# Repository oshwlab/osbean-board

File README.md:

OSBean Boards
==============
OSBean的[开源硬件](http://www.oshwa.org/)项目。

WRTnodeShield
==============
OSBean针对WRTnode的扩展板。

电路原理图和PCB均采用[KiCad](www.kicad-pcb.org)软件完成。

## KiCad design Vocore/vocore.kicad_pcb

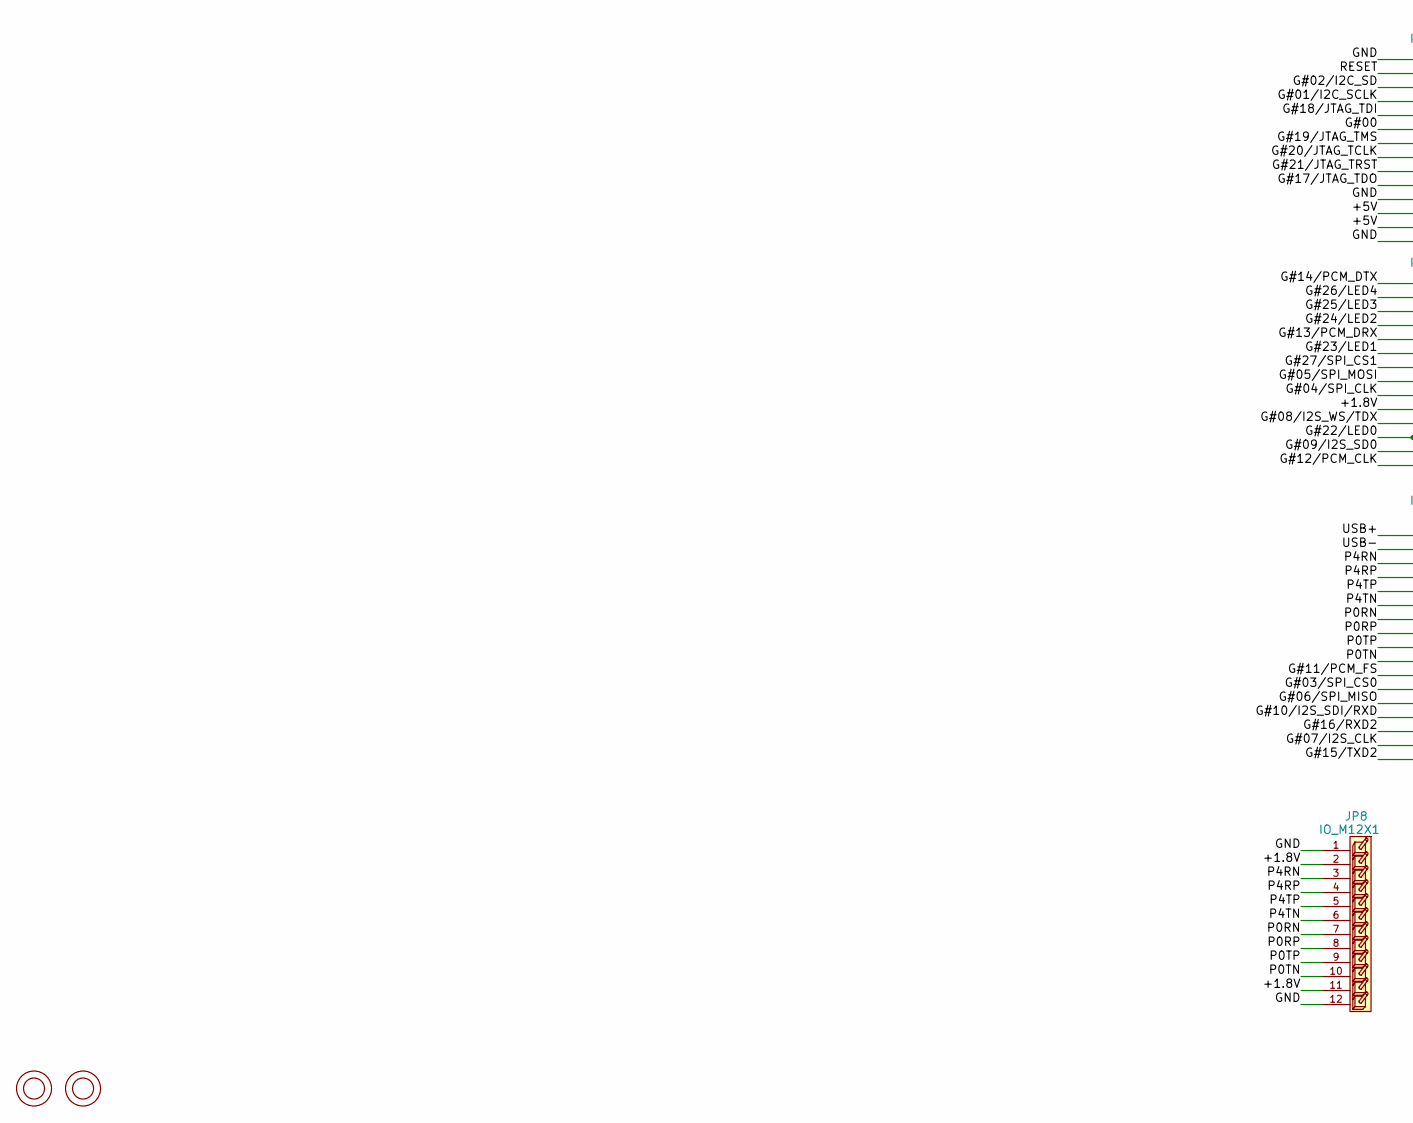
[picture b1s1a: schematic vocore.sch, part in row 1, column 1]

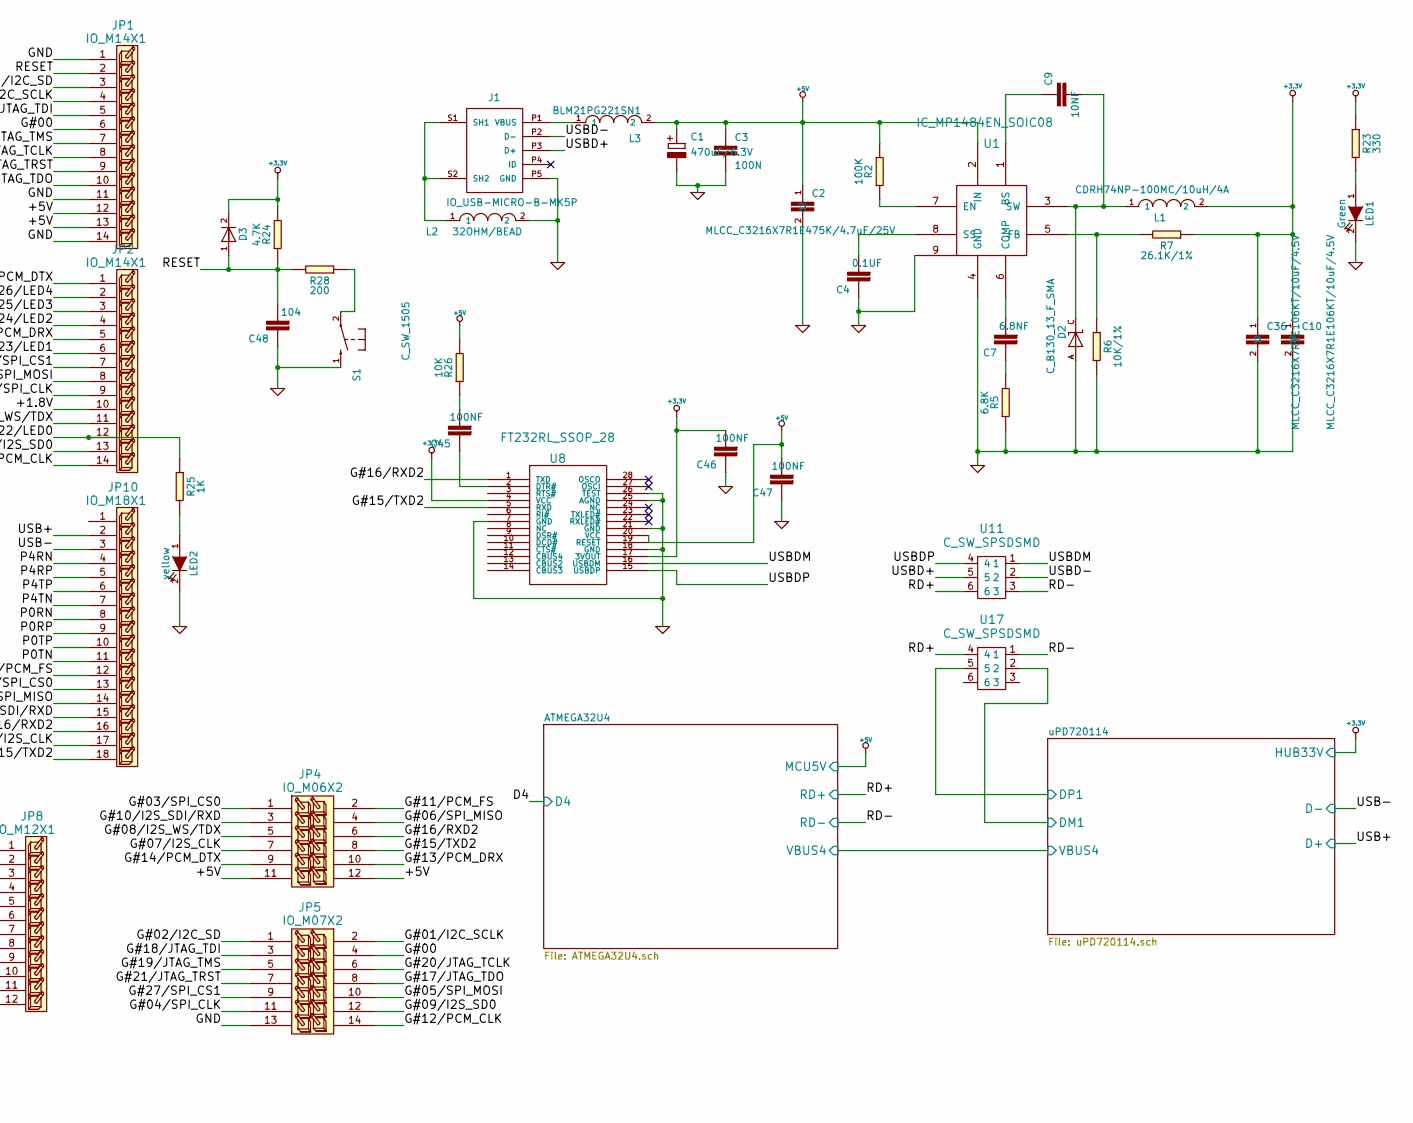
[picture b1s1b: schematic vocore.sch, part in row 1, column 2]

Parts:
C1: 470uF/6.3V; C_CPOL_SMCE
C2: MLCC_C3216X7R1E475K/4.7uF/25V; rcl-C1206
C3: 100N; C_C_0603
C4: 0.1UF; C_C_0603
C7: 6.8NF; C_C_0603
C9: 10NF; C_C_0603
C10, C36: MLCC_C3216X7R1E106KT/10uF/4.5V; rcl-C1206
C45, C46, C47: 100NF; C_C_0603
C48: 104; C_C_0603
D2: C_B130_13_F_SMA; C_B130
D3: C_DIODE-1N4148_MINIMELF
J1: IO_USB-MICRO-B-MK5P
JP1, JP2: IO_M14X1; IO-M14-1.27MM
JP4: IO_M06X2
JP5: IO_M07X2
JP8: IO_M12X1
JP10: IO_M18X1; IO-M18X1-1.27MM
L1: CDRH74NP-100MC/10uH/4A; rcl-L7070
L2: 32OHM/BEAD; rcl-L0805
L3: BLM21PG221SN1; rcl-L0805
LED1: Green; C_LED_0805
LED2: yellow; C_LED_0805
P2, P3: IO_HOLE-3.2
R2: 100K; C_R_0603
R5: 6.8K; C_R_0603
R6: 10K/1%; C_R_0603
R7: 26.1K/1%; C_R_0603
R23: 330; C_R_0603
R24: 4.7K; C_R_0603
R25: 1K; C_R_0603
R26: 10K; C_R_0603
R28: 200; C_R_0603
S1: C_SW_1505
U1: IC_MP1484EN_SOIC08
U8: FT232RL_SSOP_28
U11, U17: C_SW_SPSDSMD

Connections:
+3.3V: C10.1, C36.1, C46.2, D3.2, L1.2, R7.1, R23.1, R24.2, U8.4 (VCC), U8.17 (3VOUT); also elsewhere on the board
+5V: C1.1 (A), C2.1, C3.1, C47.2, JP1.12, JP1.13, JP4.11, JP4.12, L3.2, R2.2, R26.2, U1.2 (IN), U8.19 (RESET), U8.20 (VCC); also elsewhere on the board
/+1.8V: JP2.10, JP8.2, JP8.11
/ATMEGA32U4/RD+: U11.6, U17.4; also elsewhere on the board
/ATMEGA32U4/RD-: U11.3, U17.1; also elsewhere on the board
/G#00: JP1.6, JP5.4
/G#01/I2C_SCLK: JP1.4, JP5.2
/G#02/I2C_SD: JP1.3, JP5.1
/G#03/SPI_CS0: JP4.1, JP10.13
/G#04/SPI_CLK: JP2.9, JP5.11
/G#05/SPI_MOSI: JP2.8, JP5.10
/G#06/SPI_MISO: JP4.4, JP10.14
/G#07/I2S_CLK: JP4.7, JP10.17
/G#08/I2S_WS/TDX: JP2.11, JP4.5
/G#09/I2S_SD0: JP2.13, JP5.12
/G#10/I2S_SDI/RXD: JP4.3, JP10.15
/G#11/PCM_FS: JP4.2, JP10.12
/G#12/PCM_CLK: JP2.14, JP5.14
/G#13/PCM_DRX: JP2.5, JP4.10
/G#14/PCM_DTX: JP2.1, JP4.9
/G#15/TXD2: JP4.8, JP10.18, U8.5 (RXD)
/G#16/RXD2: JP4.6, JP10.16, U8.1 (TXD)
/G#17/JTAG_TDO: JP1.10, JP5.8
/G#18/JTAG_TDI: JP1.5, JP5.3
/G#19/JTAG_TMS: JP1.7, JP5.5
/G#20/JTAG_TCLK: JP1.8, JP5.6
/G#21/JTAG_TRST: JP1.9, JP5.7
/G#22/LED0: JP2.12, R25.1
/G#27/SPI_CS1: JP2.7, JP5.9
/P0RN: JP8.7, JP10.8
/P0RP: JP8.8, JP10.9
/P0TN: JP8.10, JP10.11
/P0TP: JP8.9, JP10.10
/P4RN: JP8.3, JP10.4
/P4RP: JP8.4, JP10.5
/P4TN: JP8.6, JP10.7
/P4TP: JP8.5, JP10.6
/RESET: C48.2, D3.1, JP1.2, R24.1, R28.2
/USBD+: J1.P3 (D+), U11.5
/USBD-: J1.P2 (D-), U11.2
/USBDM: U8.16 (USBDM), U11.1
/USBDP: U8.15 (USBDP), U11.4
/uPD720114/D+: JP10.2; also elsewhere on the board
/uPD720114/D-: JP10.3; also elsewhere on the board
/uPD720114/DM1: U17.2; also elsewhere on the board
/uPD720114/DP1: U17.5; also elsewhere on the board
GND: C1.2 (C), C2.2, C3.2, C4.1, C10.2, C36.2, C46.1, C47.1, C48.1, D2.A, J1.P5 (GND), JP1.1, JP1.11, JP1.14, JP5.13, JP8.1, JP8.12, L2.2, LED1.2 (K), LED2.2 (K), R5.1, R6.2, S1.1, U1.4 (GND), U1.9, U8.7 (GND), U8.18 (GND), U8.21 (GND), U8.25 (AGND), U8.26 (TEST); also elsewhere on the board
unnamed: LED1.1 (A), R23.2
unnamed: J1.S1 (SH1), J1.S2 (SH2), L2.1
unnamed: LED2.1 (A), R25.2
unnamed: R2.1, U1.7 (EN)
unnamed: C9.1, U1.1 (BS)
unnamed: C9.2, D2.C, L1.1, U1.3 (SW)
unnamed: R6.1, R7.2, U1.5 (FB)
unnamed: J1.P1 (VBUS), L3.1
unnamed: C4.2, U1.8 (SS)
unnamed: C7.2, U1.6 (COMP)
unnamed: C7.1, R5.2
unnamed: R28.1, S1.2
unnamed: C45.1, U8.2 (DTR#)
unnamed: C45.2, R26.1

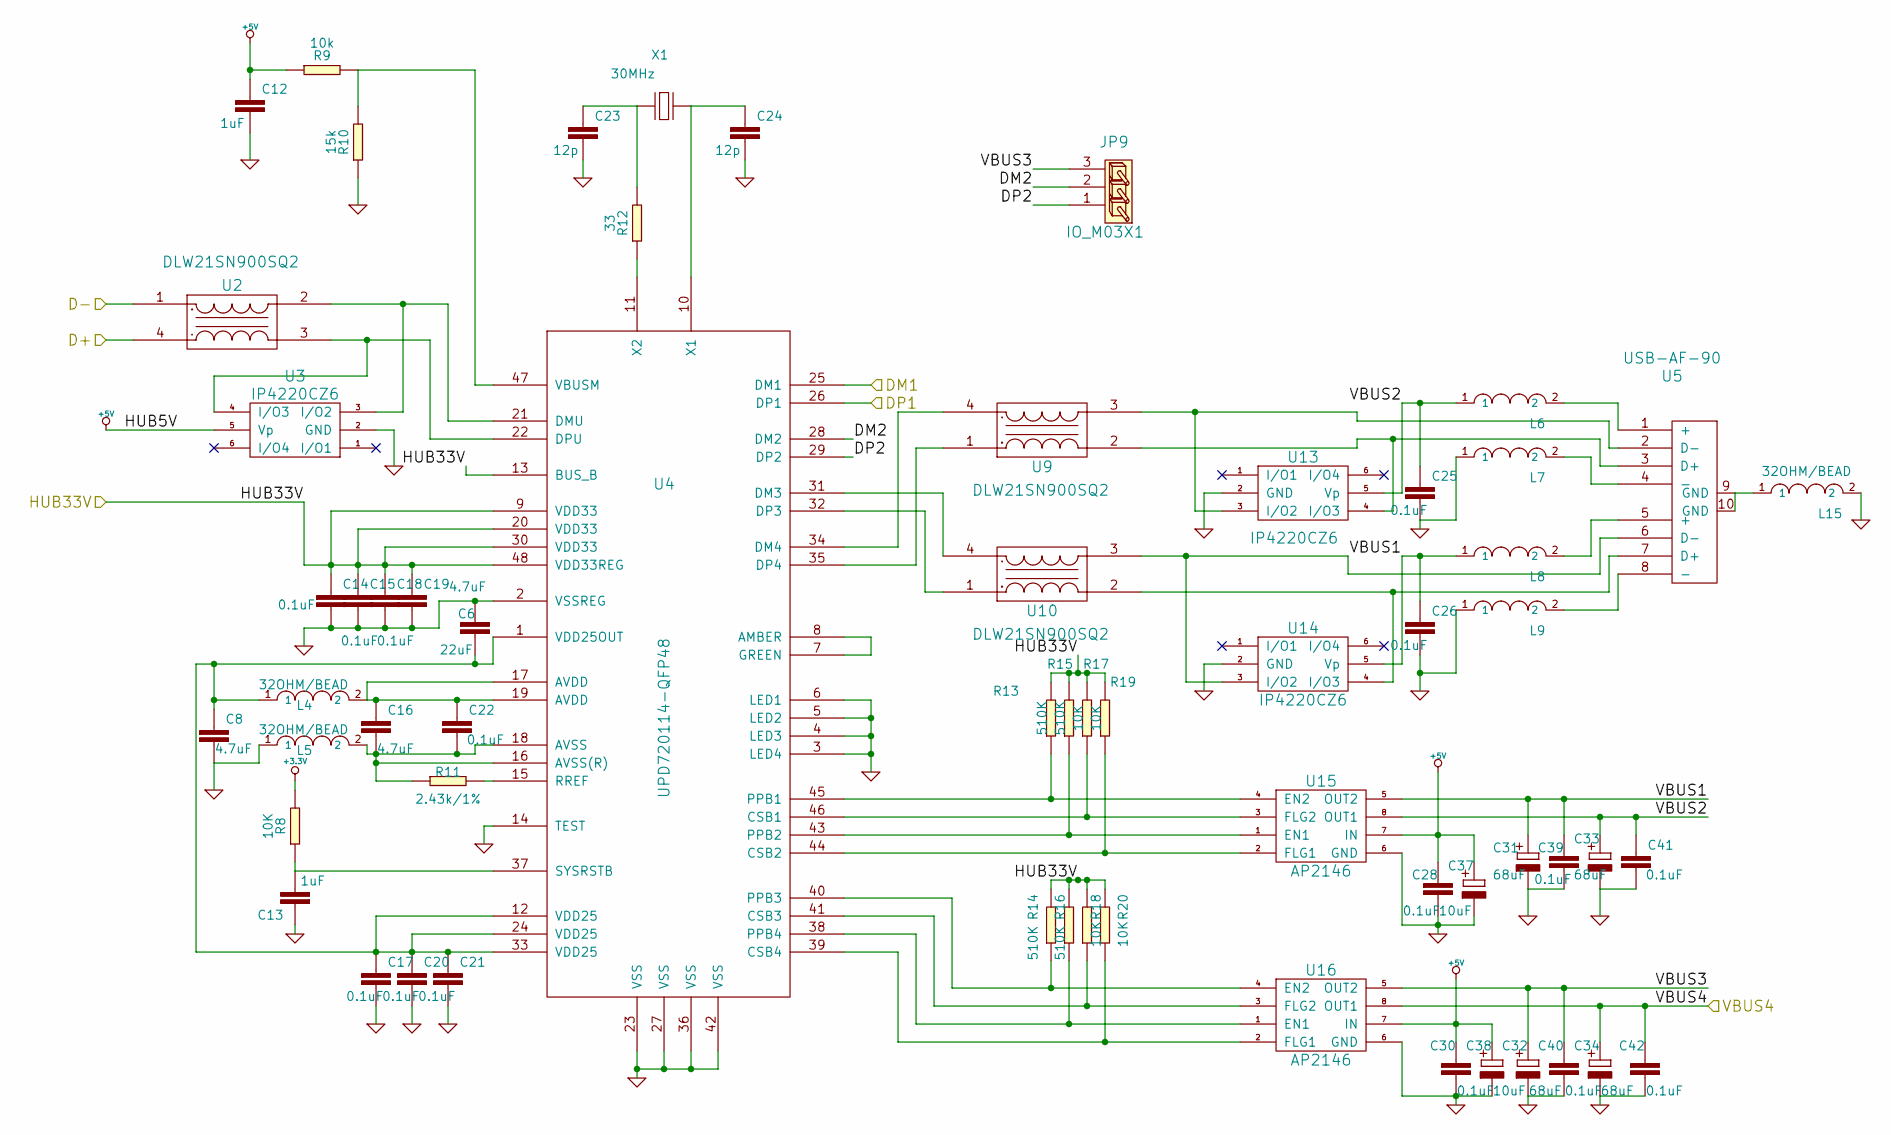
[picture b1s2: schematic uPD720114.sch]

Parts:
C6: 22uF; C_C_0603
C8, C16, C19: 4.7uF; C_C_0603
C12, C13: 1uF; C_C_0603
C14, C15, C17, C18, C20, C21, C22, C25, C26, C28, C30, C39, C40, C41, C42: 0.1uF; C_C_0603
C23, C24: 12p; C_C_0603
C31, C32, C33, C34: 68uF; C_CPOL_SMCB
C37, C38: 10uF; C_CPOL_SMCA
JP9: IO_M03X1
L4, L5, L15: 32OHM/BEAD; rcl-L0805
L6, L7, L8, L9: BLM21PG221SN1; rcl-L0805
R8, R17, R18, R19, R20: 10K; C_R_0603
R9: 10k; C_R_0603
R10: 15k; C_R_0603
R11: 2.43k/1%; C_R_0603
R12: 33; C_R_0603
R13, R14, R15, R16: 510K; C_R_0603
U2, U9, U10: DLW21SN900SQ2
U3, U13, U14: IP4220CZ6; IP4220CZ6_SOT23_6
U4: UPD720114-QFP48
U5: USB-AF-90
U15, U16: AP2146; AP1212_SOP8
X1: 30MHz; C_CRY_5.0-3.2

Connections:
+3.3V: C14.1, C15.1, C18.1, C19.1, R8.2, R13.2, R14.2, R15.2, R16.2, R17.2, R18.2, R19.2, R20.2, U4.9 (VDD33), U4.13 (BUS_B), U4.20 (VDD33), U4.30 (VDD33), U4.48 (VDD33REG); also elsewhere on the board
+5V: C12.1, C28.1, C30.1, C37.1 (+), C38.1 (+), R9.1, U3.5 (Vp), U15.7 (IN), U16.7 (IN); also elsewhere on the board
/ATMEGA32U4/VBUS4: C34.1 (A), C42.1, U16.8 (OUT1); also elsewhere on the board
/uPD720114/D+: U2.4; also elsewhere on the board
/uPD720114/D-: U2.1; also elsewhere on the board
/uPD720114/DM1: U4.25 (DM1); also elsewhere on the board
/uPD720114/DM2: JP9.2, U4.28 (DM2)
/uPD720114/DP1: U4.26 (DP1); also elsewhere on the board
/uPD720114/DP2: JP9.1, U4.29 (DP2)
/uPD720114/VBUS1: C26.1, C31.1 (A), C39.1, L8.1, U14.5 (Vp), U15.5 (OUT2)
/uPD720114/VBUS2: C25.1, C33.1 (A), C41.1, L6.1, U13.5 (Vp), U15.8 (OUT1)
/uPD720114/VBUS3: C32.1 (A), C40.1, JP9.3, U16.5 (OUT2)
GND: C6.1, C8.2, C12.2, C13.1, C14.2, C15.2, C17.2, C18.2, C19.2, C20.2, C21.2, C23.2, C24.2, C25.2, C26.2, C28.2, C30.2, C31.2 (C), C32.2 (C), C33.2 (C), C34.2 (C), C37.2 (-), C38.2 (-), C39.2, C40.2, C41.2, C42.2, L5.1, L7.1, L9.1, L15.2, R10.1, U3.2 (GND), U4.2 (VSSREG), U4.3 (LED4), U4.4 (LED3), U4.5 (LED2), U4.6 (LED1), U4.14 (TEST), U4.23 (VSS), U4.27 (VSS), U4.36 (VSS), U4.42 (VSS), U13.2 (GND), U14.2 (GND), U15.6 (GND), U16.6 (GND); also elsewhere on the board
unnamed: R11.2, U4.15 (RREF)
unnamed: U2.2, U3.3 (I/O2), U4.21 (DMU)
unnamed: U2.3, U3.4 (I/O3), U4.22 (DPU)
unnamed: L7.2, U5.4 (-)
unnamed: C13.2, R8.1, U4.37 (SYSRSTB)
unnamed: R9.2, R10.2, U4.47 (VBUSM)
unnamed: U5.7 (D+), U10.2, U14.4 (I/O3)
unnamed: U4.32 (DP3), U10.1
unnamed: U4.31 (DM3), U10.4
unnamed: L6.2, U5.1 (+)
unnamed: U5.2 (D-), U9.3, U13.3 (I/O2)
unnamed: U4.35 (DP4), U9.1
unnamed: U4.34 (DM4), U9.4
unnamed: U5.3 (D+), U9.2, U13.4 (I/O3)
unnamed: U5.6 (D-), U10.3, U14.3 (I/O2)
unnamed: U4.7 (GREEN), U4.8 (AMBER)
unnamed: C23.1, R12.2, X1.1 (C1)
unnamed: C24.1, U4.10 (X1), X1.2 (C2)
unnamed: R15.1, U4.43 (PPB2), U15.1 (EN1)
unnamed: R17.1, U4.46 (CSB1), U15.3 (FLG2)
unnamed: R19.1, U4.44 (CSB2), U15.2 (FLG1)
unnamed: R13.1, U4.45 (PPB1), U15.4 (EN2)
unnamed: R16.1, U4.38 (PPB4), U16.1 (EN1)
unnamed: R14.1, U4.40 (PPB3), U16.4 (EN2)
unnamed: R12.1, U4.11 (X2)
unnamed: R18.1, U4.41 (CSB3), U16.3 (FLG2)
unnamed: R20.1, U4.39 (CSB4), U16.2 (FLG1)
unnamed: C16.2, C22.2, L5.2, R11.1, U4.16 (AVSS(R)), U4.18 (AVSS)
unnamed: L15.1, U5.9 (GND), U5.10 (GND)
unnamed: L8.2, U5.5 (+)
unnamed: L9.2, U5.8 (-)
unnamed: C16.1, C22.1, L4.2, U4.17 (AVDD), U4.19 (AVDD)
unnamed: C6.2, C8.1, C17.1, C20.1, C21.1, L4.1, U4.1 (VDD25OUT), U4.12 (VDD25), U4.24 (VDD25), U4.33 (VDD25)

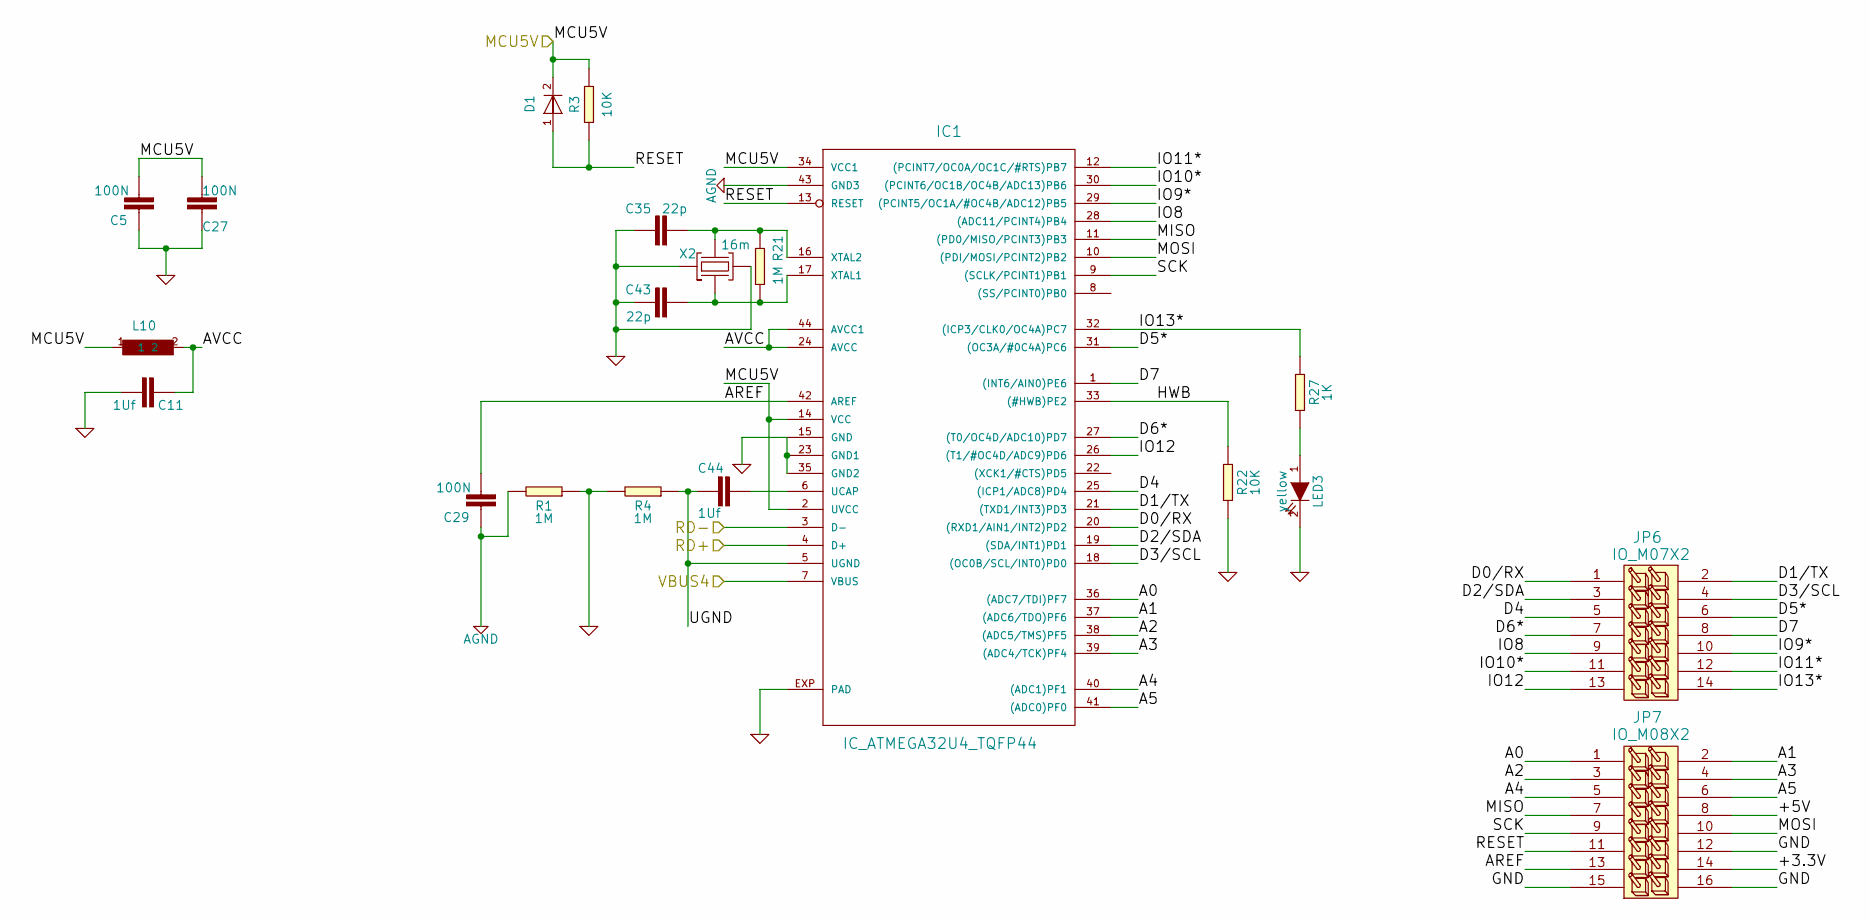
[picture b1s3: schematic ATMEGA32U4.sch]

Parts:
C5, C27, C29: 100N; C_C_0603
C11, C44: 1Uf; C_C_0603
C35, C43: 22p; C_C_0603
D1: C_DIODE-1N4148_MINIMELF
IC1: IC_ATMEGA32U4_TQFP44
JP6: IO_M07X2
JP7: IO_M08X2
L10: L-EUL0603; rcl-L0603
LED3: yellow; C_LED_0805
R1, R4, R21: 1M; C_R_0603
R3, R22: 10K; C_R_0603
R27: 1K; C_R_0603
X2: 16m; C_CRY_3.2-2.5

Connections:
+3.3V: JP7.14; also elsewhere on the board
+5V: C5.2, C27.2, D1.2, IC1.2 (UVCC), IC1.14 (VCC), IC1.34 (VCC1), JP7.8, L10.1, R3.2; also elsewhere on the board
/ATMEGA32U4/A0: IC1.36 ((ADC7/TDI)PF7), JP7.1
/ATMEGA32U4/A1: IC1.37 ((ADC6/TDO)PF6), JP7.2
/ATMEGA32U4/A2: IC1.38 ((ADC5/TMS)PF5), JP7.3
/ATMEGA32U4/A3: IC1.39 ((ADC4/TCK)PF4), JP7.4
/ATMEGA32U4/A4: IC1.40 ((ADC1)PF1), JP7.5
/ATMEGA32U4/A5: IC1.41 ((ADC0)PF0), JP7.6
/ATMEGA32U4/AREF: C29.2, IC1.42 (AREF), JP7.13
/ATMEGA32U4/AVCC: C11.1, IC1.24 (AVCC), IC1.44 (AVCC1), L10.2
/ATMEGA32U4/D0/RX: IC1.20 ((RXD1/AIN1/INT2)PD2), JP6.1
/ATMEGA32U4/D1/TX: IC1.21 ((TXD1/INT3)PD3), JP6.2
/ATMEGA32U4/D2/SDA: IC1.19 ((SDA/INT1)PD1), JP6.3
/ATMEGA32U4/D3/SCL: IC1.18 ((OC0B/SCL/INT0)PD0), JP6.4
/ATMEGA32U4/D4: IC1.25 ((ICP1/ADC8)PD4), JP6.5
/ATMEGA32U4/D5*: IC1.31 ((OC3A/#0C4A)PC6), JP6.6
/ATMEGA32U4/D6*: IC1.27 ((T0/OC4D/ADC10)PD7), JP6.7
/ATMEGA32U4/D7: IC1.1 ((INT6/AIN0)PE6), JP6.8
/ATMEGA32U4/HWB: IC1.33 ((#HWB)PE2), R22.1
/ATMEGA32U4/IO8: IC1.28 ((ADC11/PCINT4)PB4), JP6.9
/ATMEGA32U4/IO9*: IC1.29 ((PCINT5/OC1A/#OC4B/ADC12)PB5), JP6.10
/ATMEGA32U4/IO10*: IC1.30 ((PCINT6/OC1B/OC4B/ADC13)PB6), JP6.11
/ATMEGA32U4/IO11*: IC1.12 ((PCINT7/OC0A/OC1C/#RTS)PB7), JP6.12
/ATMEGA32U4/IO12: IC1.26 ((T1/#OC4D/ADC9)PD6), JP6.13
/ATMEGA32U4/IO13*: IC1.32 ((ICP3/CLK0/OC4A)PC7), JP6.14, R27.1
/ATMEGA32U4/MISO: IC1.11 ((PD0/MISO/PCINT3)PB3), JP7.7
/ATMEGA32U4/MOSI: IC1.10 ((PDI/MOSI/PCINT2)PB2), JP7.10
/ATMEGA32U4/RD+: IC1.4 (D+); also elsewhere on the board
/ATMEGA32U4/RD-: IC1.3 (D-); also elsewhere on the board
/ATMEGA32U4/RESET: D1.1, IC1.13 (RESET), JP7.11, R3.1
/ATMEGA32U4/SCK: IC1.9 ((SCLK/PCINT1)PB1), JP7.9
/ATMEGA32U4/UGND: C44.2, IC1.5 (UGND), R4.1
/ATMEGA32U4/VBUS4: IC1.7 (VBUS); also elsewhere on the board
AGND: C29.1, IC1.43 (GND3), R1.2
GND: C5.1, C11.2, C27.1, C35.1, C43.1, IC1.15 (GND), IC1.23 (GND1), IC1.35 (GND2), IC1.EXP (PAD), JP7.12, JP7.15, JP7.16, LED3.2 (K), R1.1, R4.2, R22.2, X2.2 (GND@1), X2.4 (GND@2); also elsewhere on the board
unnamed: C44.1, IC1.6 (UCAP)
unnamed: LED3.1 (A), R27.2
unnamed: C43.2, IC1.17 (XTAL1), R21.1, X2.1 (C1)
unnamed: C35.2, IC1.16 (XTAL2), R21.2, X2.3 (C2)

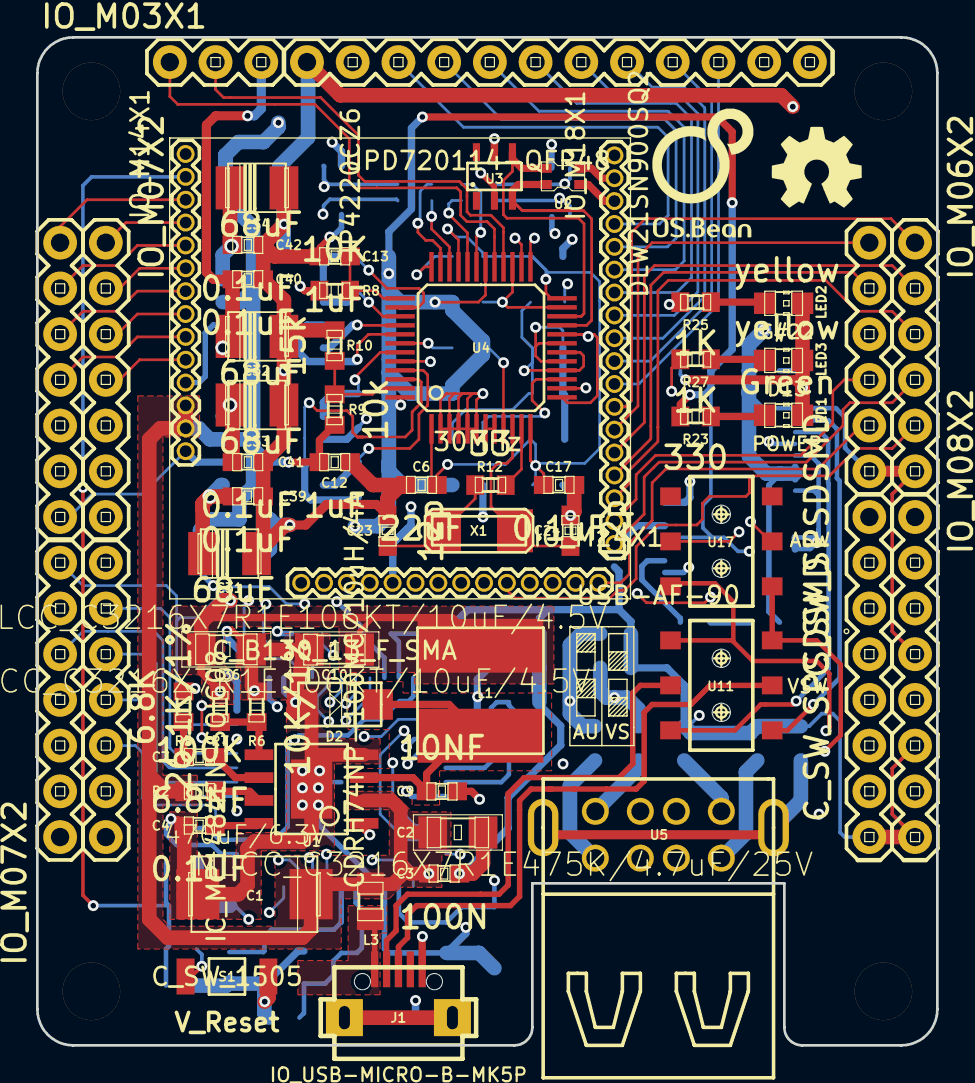
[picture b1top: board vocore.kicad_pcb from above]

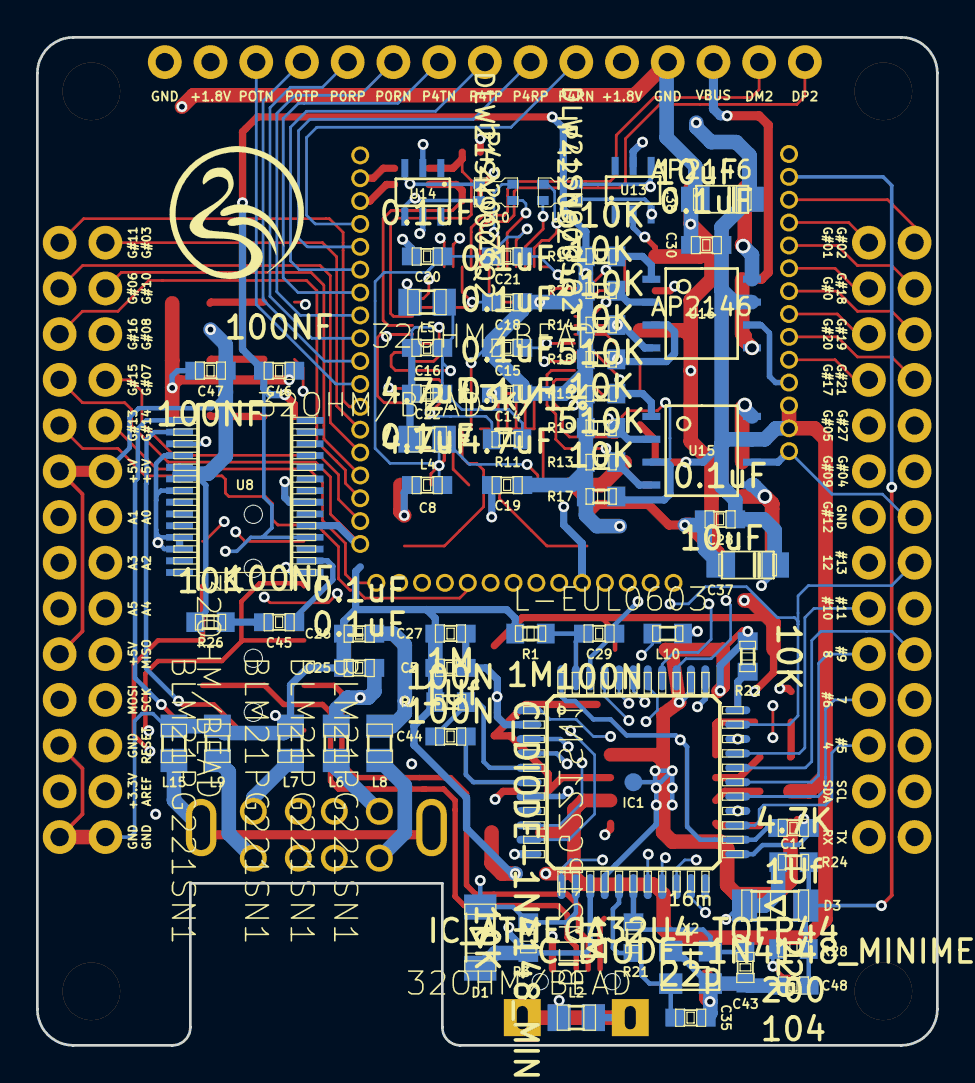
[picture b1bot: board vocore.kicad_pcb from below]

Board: 4 copper layers, 50.0 x 56.0 mm, 126 parts (63 on the bottom side), 133 nets.

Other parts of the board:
P3#2, P3#3: PINHOLE; IO_HOLE-3.2
VAL: REF; OS.Bean

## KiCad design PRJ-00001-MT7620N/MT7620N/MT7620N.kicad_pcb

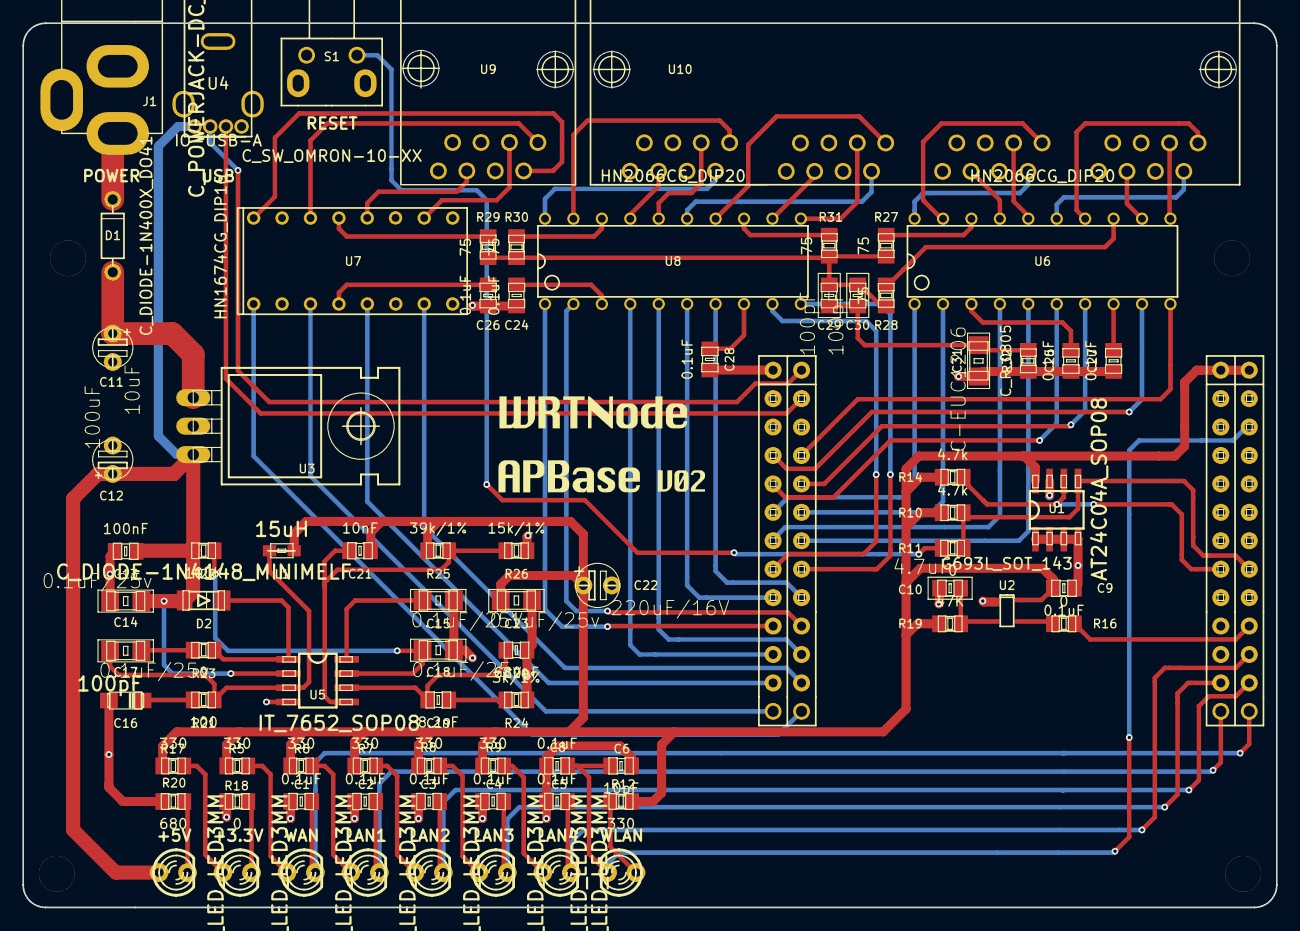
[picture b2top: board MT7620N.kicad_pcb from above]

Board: 2 copper layers, 112.0 x 79.0 mm, 86 parts (1 on the bottom side), 89 nets.

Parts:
C1, C2, C3, C4, C5, C8, C9, C24, C25, C26, C27, C28: 0.1uF; C_C_0805
C6: 10pF; C_C_0805
C10: 4.7uF; rcl-C0805
C11: 100uF; C_CPOL-EUE_2.5-5
C12: 10uF; C_CPOL-EUE_2.5-5
C13: 100nF; C_C_0805
C14, C17, C18, C23: 0.1uF/25v; rcl-C1206
C15: 0.1uF/25V; rcl-C1206
C16: 100pF; C_CPOL_SMCA
C19: 8.2nF; C_C_0805
C20: 680pF; C_C_0805
C21: 10nF; C_C_0805
C22: 220uF/16V; C_CPOL-EUE_2.5-6
C29, C30: 100pF; rcl-C0805
C31: C-EUC1206; rcl-C1206
D1: C_DIODE-1N400X_DO41; C_DIODE-1N4148_DO41
D2: C_DIODE-1N4148_MINIMELF
J1: C_POWERJACK-DC_2,1MM
JP1, JP2: IO_FM13X2
L1: 15uH; C_L-CBF_0805
LED1, LED2, LED3, LED4, LED5, LED6, LED7, LED9: C_LED_LED3MM
P1, P2, P3, P4: IO_HOLE-3.2
R5, R6, R7, R8, R9, R12, R17: 330; C_R_0805
R10, R14: 4.7k; C_R_0805
R11, R16, R18, R23: 0; C_R_0805
R19: 47K; C_R_0805
R20: 680; C_R_0805
R21: 100; C_R_0805
R22: 100K; C_R_0805
R24: 3k/1%; C_R_0805
R25: 39k/1%; C_R_0805
R26: 15k/1%; C_R_0805
R27, R28, R29, R30, R31: 75; C_R_0805
R32: C_R_0805
S1: C_SW_OMRON-10-XX; SW_6*6*6
U1: AT24C04A_SOP08
U2: G693L_SOT_143
U3: IC_LM340_TO_220
U4: IO-USB-A
U5: IT_7652_SOP08
U6, U8: HN2066CG_DIP20
U7: HN1674CG_DIP16
U9: IO_RJ45X1-JACK; IO_RJ45X1
U10: RJ45-4*1
VAL: mini6

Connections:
+3.3V: C9.1, C21.1, C22.+, C23.1, JP1.1, JP1.2, L1.2, R5.2, R6.2, R7.2, R8.2, R9.2, R10.2, R12.2, R14.2, R17.2, R19.2, R25.2, U1.8, U2.4
+5V: C12.+, C13.1, C14.1, D2.1, LED7.2, R22.1, U3.3, U4.1, U5.2
/D+: JP2.4, U4.3
/D-: JP2.2, U4.2
/I2C_SCLK: JP1.15, R14.1, U1.6
/I2C_SD: JP1.16, R10.1, R11.2, U1.5
/LINK0: C5.1, JP1.22, LED5.1
/LINK1: C4.1, JP1.23, LED4.1
/LINK2: C3.1, JP1.24, LED3.1
/LINK3: C2.1, JP1.25, LED2.1
/LINK4: C1.1, JP1.26, LED1.1
/RST_PBC: R11.1, S1.1
/WDT_RST_N: JP1.20, R16.1
/WLAN/RXIN0: JP2.7, U6.9
/WLAN/RXIN1: JP2.11, U6.1
/WLAN/RXIN2: JP2.15, U8.9
/WLAN/RXIN3: JP2.19, U8.1
/WLAN/RXIN4: JP2.23, U7.5
/WLAN/RXIP0: JP2.8, U6.10
/WLAN/RXIP1: JP2.12, U6.2
/WLAN/RXIP2: JP2.16, U8.10
/WLAN/RXIP3: JP2.20, U8.2
/WLAN/RXIP4: JP2.24, U7.7
/WLAN/TXON0: JP2.9, U6.6
/WLAN/TXON1: JP2.13, U6.4
/WLAN/TXON2: JP2.17, U8.6
/WLAN/TXON3: JP2.21, U8.4
/WLAN/TXON4: JP2.26, U7.1
/WLAN/TXOP0: JP2.10, U6.7
/WLAN/TXOP1: JP2.14, U6.5
/WLAN/TXOP2: JP2.18, U8.7
/WLAN/TXOP3: JP2.22, U8.5
/WLAN/TXOP4: JP2.25, U7.3
/WLED_N: C6.1, C8.1, JP1.6, LED6.1
GND: C1.2, C2.2, C3.2, C4.2, C5.2, C6.2, C8.2, C9.2, C10.2, C11.-, C12.-, C13.2, C14.2, C15.2, C16.2, C18.2, C20.2, C22.-, C23.2, C24.2, C25.2, C26.2, C27.2, C28.2, C31.2, J1.1, J1.3, JP1.3, JP1.4, JP1.5, JP1.21, JP2.1, JP2.6, R18.1, R20.1, R24.1, R26.1, R32.2, S1.2, S1.3, S1.4, U1.1, U1.2, U1.3, U1.4, U1.7, U2.1, U3.2, U4.4, U4.5, U4.6, U4.7, U5.4
unnamed: LED1.2, R5.1
unnamed: LED9.1, R18.2
unnamed: LED9.2, R17.1
unnamed: LED6.2, R12.1
unnamed: LED5.2, R9.1
unnamed: LED4.2, R8.1
unnamed: LED3.2, R7.1
unnamed: LED2.2, R6.1
unnamed: C10.1, R19.1, U2.2
unnamed: R16.2, U2.3
unnamed: C11.+, D1.C, U3.1
unnamed: LED7.1, R20.2
unnamed: D1.A, J1.2
unnamed: C19.1, C20.1, U5.6
unnamed: C16.1, R21.1
unnamed: C19.2, R24.2
unnamed: C18.1, R22.2, U5.7
unnamed: C17.1, L1.1, R21.2, U5.3
unnamed: D2.2, R23.2, U5.1
unnamed: C17.2, R23.1
unnamed: C21.2, R25.1, R26.2, U5.5
unnamed: C15.1, U5.8
unnamed: U8.12, U10.14
unnamed: U8.14, U10.9
unnamed: U6.20, U10.18
unnamed: U8.11, U10.11
unnamed: U8.15, U10.10
unnamed: U8.16, U10.3
unnamed: U8.17, U10.6
unnamed: U8.19, U10.1
unnamed: R31.1, U8.13
unnamed: R30.1, U8.18
unnamed: U6.16, U10.19
unnamed: U6.17, U10.22
unnamed: U6.19, U10.17
unnamed: U8.20, U10.2
unnamed: U7.10, U9.3
unnamed: U7.12, U9.6
unnamed: U7.14, U9.1
unnamed: U7.16, U9.2
unnamed: U6.11, U10.27
unnamed: U6.15, U10.26
unnamed: U6.14, U10.25
unnamed: U6.12, U10.30
unnamed: C29.2, C30.2, C31.1, R32.1
unnamed: R27.1, U6.18
unnamed: C29.1, C30.1, R27.2, R28.2, R29.2, R30.2, R31.2
unnamed: R29.1, U7.13
unnamed: R28.1, U6.13
unnamed: C27.1, U6.8
unnamed: C24.1, U8.3
unnamed: C28.1, U8.8
unnamed: C25.1, U6.3
unnamed: C26.1, U7.4

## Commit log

2014-11-10 Add license document.
    We use CC-SA 3.0 for this work.
2014-11-14 Remove duplicated files.
2014-11-14 Remove documentation file.
2014-11-14 Remove backup files.
2014-11-14 修改项目描述和协议文档
2014-11-14 LICENSE.txt改名为LICENSE.md
2014-11-14 加入KiCad描述部分。
2014-11-14 添加WRTnode各版本PCB
2014-11-20 修改原理图及PCB
2014-11-21 布线完成一部分
2014-11-22 Rename to board directory.
2014-11-22 Move files to top directory.
2014-11-22 Add lib and doc directories.
2014-11-26 添加完整原理图及PCB
2014-11-26 整理到根目录
2014-11-27 保存AREF引脚没外引版本
2014-11-27 生成gerber文件并整理目录
2014-12-23 添加原理图PDF文档
2014-12-30 整理目录
2014-12-30 添加Vocore
2015-01-14 Vocore第二版修改完成
2015-01-26 更新 Vocore schematic.pdf
2015-03-10 modify PCB
